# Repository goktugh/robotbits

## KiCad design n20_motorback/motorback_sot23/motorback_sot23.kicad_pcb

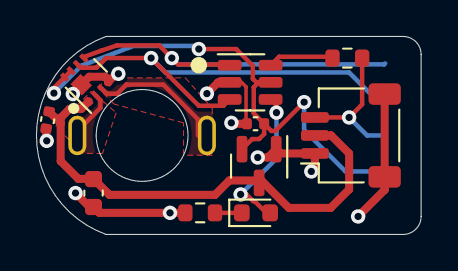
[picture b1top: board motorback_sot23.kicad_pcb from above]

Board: 2 copper layers, 21.4 x 11.0 mm, 13 parts (1 on the bottom side), 11 nets.

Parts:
C1: 10uF; C_0603_1608Metric
C2, C3: 1uF; C_0402_1005Metric
D1: LED; LED_0603_1608Metric
J1: Servo wire input; JST_SH_SM03B-SRSS-TB_1x03-1MP_P1.00mm_Horizontal
J2, J3: Conn_01x01_Male; motorpad
J4: prog_pins; pogopins_5
R1, R2: 680R; R_0603_1608Metric
U1: DRV8837DSGR; drv8837_custom
U2: ATtiny4-TS; SOT-23-6
U3: AIC1734-33GUTR; SOT-23

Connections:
/MOTORF: J4.4, U1.6 (IN1), U2.3 (PB1)
/MOTOROUT1: J2.1, U1.2 (OUT1)
/MOTOROUT2: J3.1, U1.3 (OUT2)
/MOTORR: J4.5, U1.5 (IN2), U2.1 (PB0)
/PWMR: R2.2, U2.6 (~RESET~/PB3)
/VLOGIC: C3.1, J4.2, U1.7 (~SLEEP), U1.8 (VCC), U2.5 (VCC), U3.2 (VO)
BLINKY: D1.2 (A), U2.4 (PB2)
GND: C1.2, C2.2, C3.2, J1.1, J1.MP, J4.1, R1.1, U1.4 (GND), U1.9 (GND), U2.2 (GND), U3.1 (GND)
unnamed: D1.1 (K), R1.2
PWMIN: J1.3, J4.3, R2.1
VBAT: C1.1, C2.1, J1.2, U1.1 (VM), U3.3 (VI)

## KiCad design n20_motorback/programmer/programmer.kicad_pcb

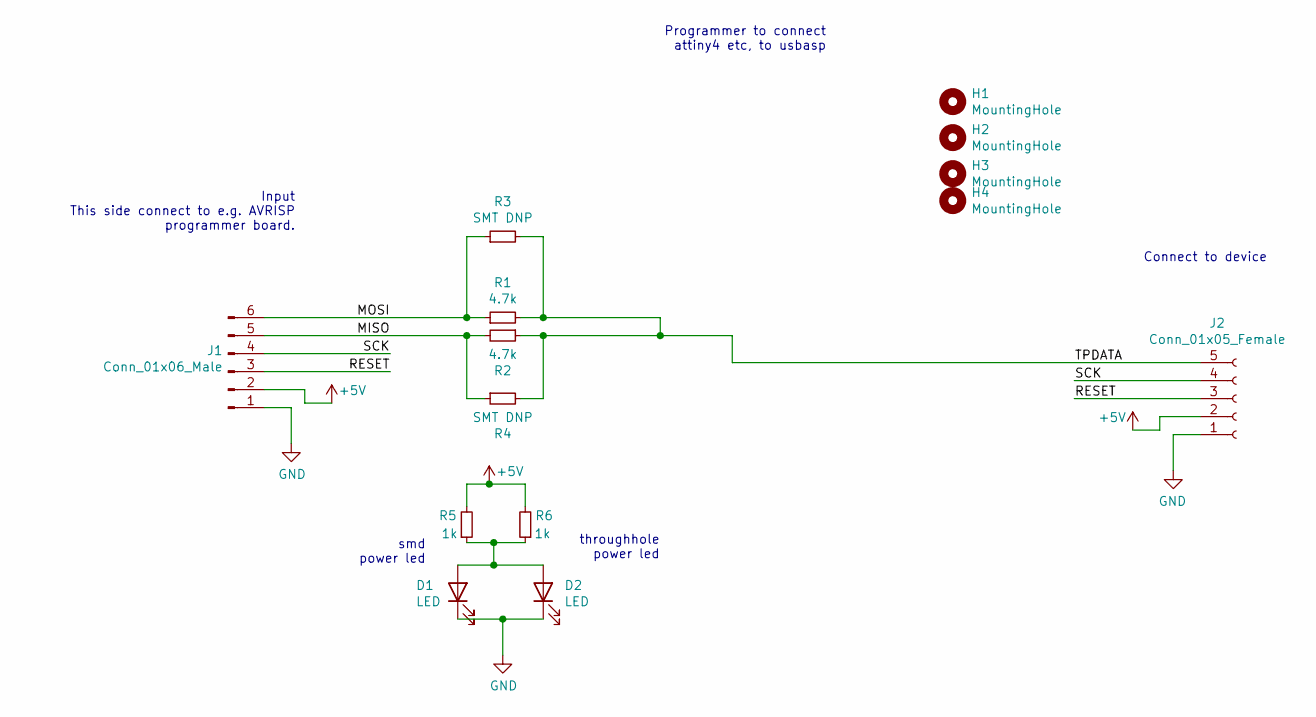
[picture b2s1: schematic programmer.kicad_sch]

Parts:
D1: LED; LED_0805_2012Metric_Pad1.15x1.40mm_HandSolder
D2: LED; LED_D5.0mm
H1, H2, H3, H4: MountingHole; MountingHole_3.2mm_M3
J1: Conn_01x06_Male; PinHeader_1x06_P2.54mm_Vertical
J2: Conn_01x05_Female; PinHeader_1x05_P2.00mm_Vertical
R1, R2: 4.7k; R_Axial_DIN0207_L6.3mm_D2.5mm_P7.62mm_Horizontal
R3, R4: SMT DNP; R_0805_2012Metric_Pad1.20x1.40mm_HandSolder
R5: 1k; R_0805_2012Metric_Pad1.20x1.40mm_HandSolder
R6: 1k; R_Axial_DIN0207_L6.3mm_D2.5mm_P7.62mm_Horizontal

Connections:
+5V: J1.2, J2.2, R5.2, R6.2
/MISO: J1.5, R2.2, R4.1
/MOSI: J1.6, R1.1, R3.1
/RESET: J1.3, J2.3
/SCK: J1.4, J2.4
/TPDATA: J2.5, R1.2, R2.1, R3.2, R4.2
GND: D1.1 (K), D2.1 (K), J1.1, J2.1
unnamed: D1.2 (A), D2.2 (A), R5.1, R6.1

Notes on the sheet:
Input This side connect to e.g. AVRISP programmer board.
smd power led
throughhole power led
Programmer to connect attiny4 etc, to usbasp
Connect to device

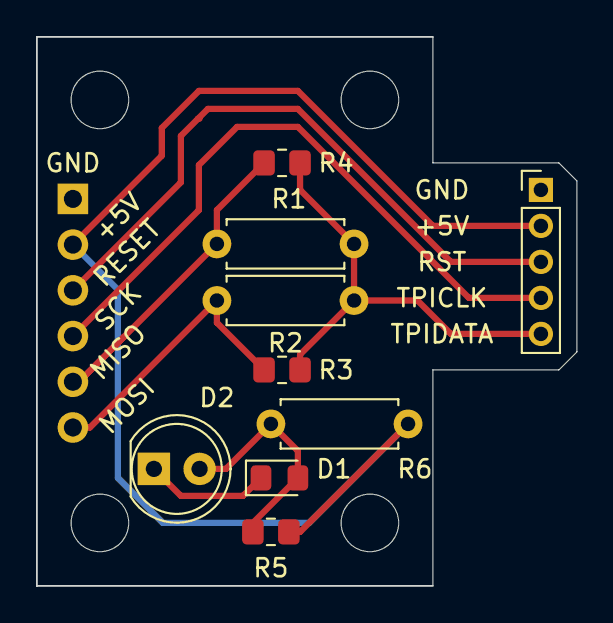
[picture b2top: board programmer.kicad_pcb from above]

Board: 2 copper layers, 30.0 x 30.5 mm, 14 parts (1 on the bottom side), 8 nets.
